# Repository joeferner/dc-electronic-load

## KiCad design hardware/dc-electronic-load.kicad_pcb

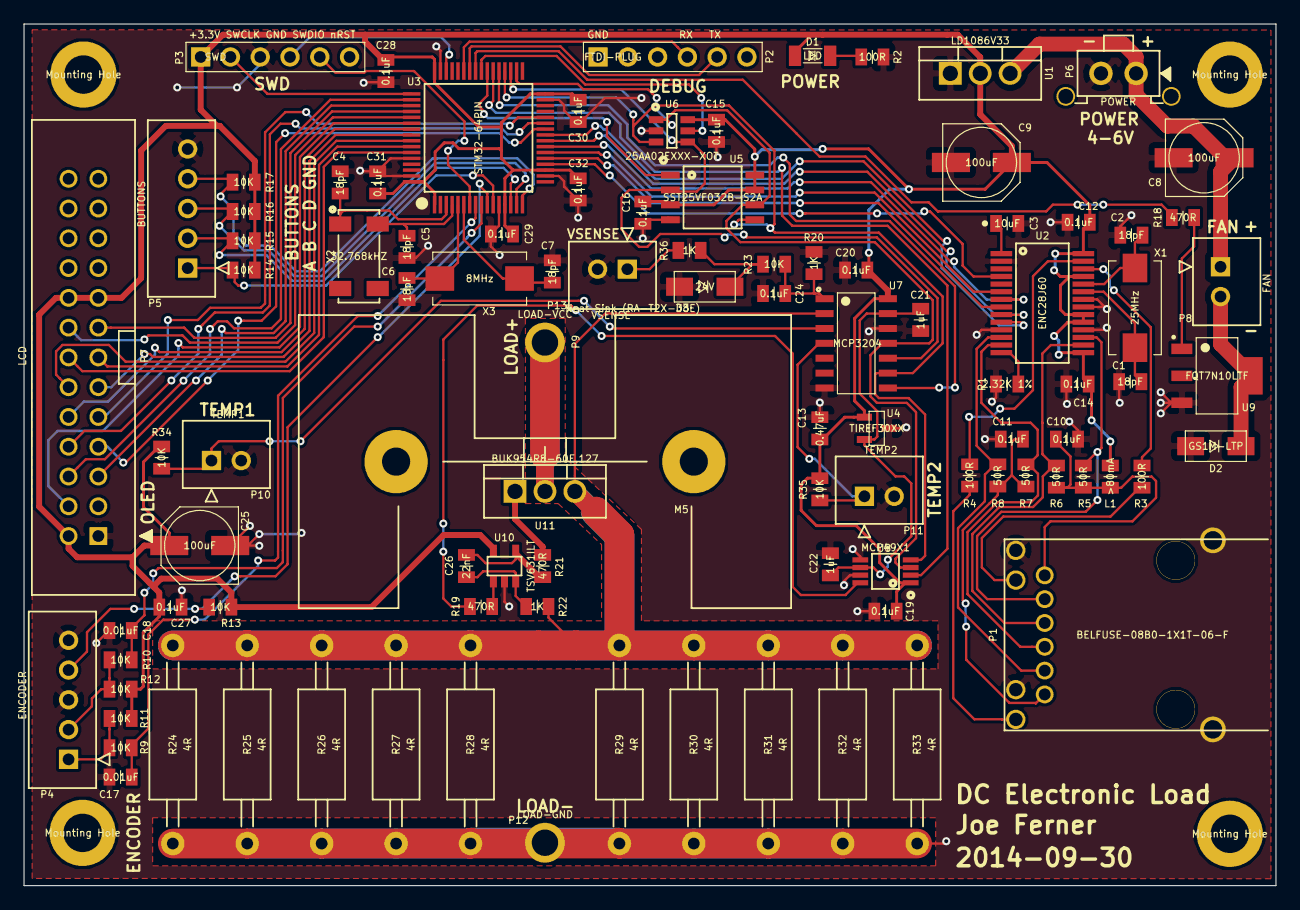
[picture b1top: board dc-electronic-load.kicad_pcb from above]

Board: 2 copper layers, 106.8 x 73.5 mm, 107 parts (0 on the bottom side), 78 nets.

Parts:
C1, C2, C4, C5, C6, C7: 18pF; CAPC2012X100N
C3: 10uF; CAPCP2012X100N
C8, C9, C25: 100uF; CAPAE660X790N
C10, C11, C12, C14, C15, C16, C19, C20, C24, C27, C28, C29, C30, C31, C32: 0.1uF; CAPC2012X100N
C13: 0.47uF; CAPC2012X100N
C17, C18: 0.01uF; CAPC2012X100N
C21, C22: 1uF; CAPC2012X100N
C26: 22nF; CAPC2012X100N
D1: LED; LEDC3216X100N
D2: GS1M-LTP; DIOM5226X220N
D3: 24V; DIOM5226X220N
L1: >80mA; RESC2012X100N
M1, M2, M3, M4: Mounting Hole; MTGNP565H328Z565P
M5: Heat Sink (RA-T2X-38E); OHMITE-R-SERIES
M6: Power Entry Connector; EMPTY
M7: Enclosure (8.36x9.11x3.15); EMPTY
M8: Fan (50mm x 10mm); EMPTY
M9: Fan Guard; EMPTY
P1: BELFUSE-08B0-1X1T-06-F; BEL-FUSE-08B0-1X1T-06-F
P2: FTDI-PLUG; HDRV6W66P254_1X6_1524X249X838P
P3: SWD; HDRV6W66P254_1X6_1524X249X838P
P4: ENCODER; JST-B5B-XH-A
P5: BUTTONS; JST-B5B-XH-A
P6: POWER; TECONN-2-1445050-2
P7: LCD; SHDRV26W100P254_2X13_4052X880X910P
P8: FAN; JST-B2B-XH-A
P9: LOAD-VCC; PAD205P
P10: TEMP1; JST-B2B-XH-A
P11: TEMP2; JST-B2B-XH-A
P12: LOAD-GND; PAD205P
P13: VSENSE; JST-B2B-XH-A
R1: 2.32K 1%; RESC2012X100N
R2, R3, R4: 100R; RESC2012X100N
R5, R6, R7, R8: 50R; RESC2012X100N
R9, R10, R11, R12, R13, R14, R15, R16, R17, R23, R34, R35: 10K; RESC2012X100N
R18, R19, R21: 470R; RESC2012X100N
R20, R22, R36: 1K; RESC2012X100N
R24, R25, R26, R27, R28, R29, R30, R31, R32, R33: 4R; RESAD1690W80L890D400P
U1: LD1086V33; TO255P460X1020X1925-3P
U2: ENC28J60; SOP65P780X200-28N
U3: STM32-64PIN; QFP50P1200X1200X160-64N
U4: TIREF30XX; SOT95P237X112_123-3N
U5: SST25VF032B-S2A; SOIC127P790X216-8N
U6: 25AA02EXXX-XOT; SOT95P270X145-6N
U7: MCP3204; SOIC127P600X175-14N
U8: MCP49X1; SOP65P490X110-8N
U9: FQT7N10LTF; SOT230P700X180-4N
U10: TSV631ILT; SOT95P280X100-5N
U11: BUK954R8-60E,127; TO255P460X1020X1925-3P
X1: 25MHz; XTAL8045X200N
X2: 32.768kHZ; SOJ550P370X240-4N
X3: 8MHz; XTAL8045X200N

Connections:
+3.3V: C9.1, C12.1, C13.1, C14.1, C15.1, C16.1, C19.1, C20.1, C25.1, C27.1, C28.1, C29.1, C30.1, C31.1, C32.1, D1.1, L1.1, P3.1, P7.2, P7.17, P7.18, R11.1, R12.1, R13.1, R14.1, R15.1, R16.1, R17.1, R34.2, R35.2, U1.2, U2.15, U2.19, U2.20, U2.25, U2.28, U3.1, U3.13, U3.19, U3.32, U3.48, U3.64, U4.1, U5.3, U5.7, U5.8, U6.6, U7.14, U8.1, U10.5
+5V: C8.1, P6.1, P8.1, U1.3
/ADCCS: U3.37, U7.8
/BUTTONA: P5.1, R14.2, U3.11
/BUTTONB: P5.2, R15.2, U3.14
/BUTTONC: P5.3, R16.2, U3.15
/BUTTOND: P5.4, R17.2, U3.16
/DACCS: U3.38, U8.2
/DEBUGRX: P2.4, U3.43
/DEBUGTX: P2.5, U3.42
/ENC28J60CS: U2.9, U3.24
/ENC28J60INT: U2.4, U3.20
/ENC28J60RESET: U2.10, U3.25
/ENCODERA: C17.1, R9.2, U3.8
/ENCODERB: C18.1, R10.2, U3.9
/ENCODERBUTTON: P4.4, R13.2, U3.10
/FAN: R18.2, U3.41
/FLASHCS: U3.39, U5.1
/ISENSE: R22.1, R24.1, R25.1, R26.1, R27.1, R28.1, R29.1, R30.1, R31.1, R32.1, R33.1, U7.2, U11.3
/LCDCS: P7.16, U3.53
/LCDDATA0: P7.7, U3.26
/LCDDATA1: P7.8, U3.27
/LCDDATA2: P7.9, U3.28
/LCDDATA3: P7.10, U3.55
/LCDDATA4: P7.11, U3.56
/LCDDATA5: P7.12, U3.57
/LCDDATA6: P7.13, U3.58
/LCDDATA7: P7.14, U3.59
/LCDDC: P7.4, U3.54
/LCDEN: P7.6, U3.50
/LCDRESET: P7.15, U3.52
/LCDRW: P7.5, U3.51
/MACCS: U3.40, U6.5
/SPI1MISO: U2.6, U3.22
/SPI1MOSI: U2.7, U3.23
/SPI1SCK: U2.8, U3.21
/SPI2MISO: U3.35, U5.2, U6.4, U7.10
/SPI2MOSI: U3.36, U5.5, U6.3, U7.9, U8.4
/SPI2SCK: U3.34, U5.6, U6.1, U7.11, U8.3
/SWCLK: P3.2, U3.49
/SWDIO: P3.4, U3.46
/TEMP1: P10.1, R34.1, U7.3
/TEMP2: P11.1, R35.1, U7.4
/VREF: C21.1, C22.1, U4.2, U7.13, U8.6
/VSENSE: C24.1, R20.2, R23.2, U7.1
/nRST: P3.5, U3.7
GNDPWR: C1.2, C2.2, C3.2, C4.2, C5.2, C6.2, C7.2, C8.2, C9.2, C10.2, C11.2, C12.2, C13.2, C14.2, C15.2, C16.2, C17.2, C18.2, C19.2, C20.2, C21.2, C22.2, C24.2, C25.2, C27.2, C28.2, C29.2, C30.2, C31.2, C32.2, D2.1, D3.1, P1.7, P1.9, P2.1, P3.3, P4.3, P4.5, P5.5, P6.2, P7.1, P10.2, P11.2, P12.1, P13.2, R1.2, R2.2, R20.1, R24.2, R25.2, R26.2, R27.2, R28.2, R29.2, R30.2, R31.2, R32.2, R33.2, U1.1, U2.2, U2.11, U2.18, U2.21, U2.22, U3.12, U3.18, U3.31, U3.47, U3.60, U3.63, U4.3, U5.4, U6.2, U7.7, U7.12, U8.5, U8.7, U9.3, U10.2
unnamed: C1.1, U2.23, X1.1
unnamed: C2.1, U2.24, X1.2
unnamed: C3.1, U2.1
unnamed: C4.1, U3.3, X2.1
unnamed: C5.1, U3.4, X2.4
unnamed: C6.1, U3.5, X3.1
unnamed: C7.1, U3.6, X3.2
unnamed: C10.1, L1.2, P1.1, R5.2, R6.1
unnamed: C11.1, P1.6, R7.2, R8.1
unnamed: C26.1, R21.2, U10.4
unnamed: C26.2, R22.2, U10.3
unnamed: D1.2, R2.1
unnamed: D2.2, P8.2, U9.4
unnamed: D3.2, R23.1, R36.2
unnamed: P1.2, R5.1, U2.17
unnamed: P1.3, R6.2, U2.16
unnamed: P1.4, R7.1, U2.13
unnamed: P1.5, R8.2, U2.12
unnamed: P1.8, R3.1
unnamed: P1.10, R4.1
unnamed: P4.1, R9.1, R11.2
unnamed: P4.2, R10.1, R12.2
unnamed: P9.1, U11.2
unnamed: P13.1, R36.1
unnamed: R1.1, U2.14
unnamed: R3.2, U2.26
unnamed: R4.2, U2.27
unnamed: R18.1, U9.1
unnamed: R19.1, U10.1
unnamed: R19.2, U8.8
unnamed: R21.1, U11.1

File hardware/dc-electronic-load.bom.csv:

,Reference, Value, Footprint, Datasheet, MfgPartNumber, Mfg,
x,C1,18pF,klib:CAPC2012X100N,,,,
x,C2,18pF,klib:CAPC2012X100N,,,,
x,C3,10uF,klib:CAPCP2012X100N,,,,
x,C4,18pF,klib:CAPC2012X100N,,,,
x,C5,18pF,klib:CAPC2012X100N,,,,
x,C6,18pF,klib:CAPC2012X100N,,,,
x,C7,18pF,klib:CAPC2012X100N,,,,
x,C8,100uF,klib:CAPAE660X790N,,,,
x,C9,100uF,klib:CAPAE660X790N,,,,
x,C10,0.1uF,klib:CAPC2012X100N,,,,
x,C11,0.1uF,klib:CAPC2012X100N,,,,
x,C12,0.1uF,klib:CAPC2012X100N,,,,
x,C13,0.47uF,klib:CAPC2012X100N,,,,
x,C14,0.1uF,klib:CAPC2012X100N,,,,
x,C15,0.1uF,klib:CAPC2012X100N,,,,
x,C16,0.1uF,klib:CAPC2012X100N,,,,
x,C17,0.01uF,klib:CAPC2012X100N,,,,
x,C18,0.01uF,klib:CAPC2012X100N,,,,
x,C19,0.1uF,klib:CAPC2012X100N,,,,
x,C20,0.1uF,klib:CAPC2012X100N,,,,
x,C21,1uF,klib:CAPC2012X100N,,,,
x,C22,1uF,klib:CAPC2012X100N,,,,
x,C24,0.1uF,klib:CAPC2012X100N,,,,
x,C25,100uF,klib:CAPAE660X790N,,,,
x,C26,22nF,klib:CAPC2012X100N,,,,
x,C27,0.1uF,klib:CAPC2012X100N,,,,
x,C28,0.1uF,klib:CAPC2012X100N,,,,
x,C29,0.1uF,klib:CAPC2012X100N,,,,
x,C30,0.1uF,klib:CAPC2012X100N,,,,
x,C31,0.1uF,klib:CAPC2012X100N,,,,
x,C32,0.1uF,klib:CAPC2012X100N,,,,
x,D1,LED,klib:LEDC3216X100N,,,,
x,D2,GS1M-LTP,klib:DIOM5226X220N,,GS1M-LTP,,
x,D3,24V,klib:DIOM5226X220N,,,,
x,L1,>80mA,klib:RESC2012X100N,,,,
x,M1,Mounting Hole,klib:MTGNP565H328Z565P,,,,
x,M2,Mounting Hole,klib:MTGNP565H328Z565P,,,,
x,M3,Mounting Hole,klib:MTGNP565H328Z565P,,,,
x,M4,Mounting Hole,klib:MTGNP565H328Z565P,,,,
x,M5,Heat Sink (RA-T2X-38E),klib:OHMITE-R-SERIES,,,,
x,M6,Power Entry Connector,klib:EMPTY,,06AK2D,,
x,M7,Enclosure (8.36x9.11x3.15),klib:EMPTY,,616-63210-510-000,PacTec,
x,M8,Fan (50mm x 10mm),klib:EMPTY,,MB50100V2-000U-A99,Sunon Fans,
x,M9,Fan Guard,klib:EMPTY,,FG-5,Sunon Fans,
x,P1,BELFUSE-08B0-1X1T-06-F,klib:BEL-FUSE-08B0-1X1T-06-F,,,,
x,P2,FTDI-PLUG,klib:HDRV6W66P254_1X6_1524X249X838P,,,,
x,P3,SWD,klib:HDRV6W66P254_1X6_1524X249X838P,,,,
x,P4,ENCODER,klib:JST-B5B-XH-A,,B5B-XH-A(LF)(SN),,
x,P5,BUTTONS,klib:JST-B5B-XH-A,,B5B-XH-A(LF)(SN),,
x,P6,POWER,klib:TECONN-2-1445050-2,,,,
x,P7,LCD,klib:SHDRV26W100P254_2X13_4052X880X910P,,,,
x,P8,FAN,klib:JST-B2B-XH-A,,,,
x,P9,LOAD-VCC,klib:PAD205P,,,,
x,P10,TEMP1,klib:JST-B2B-XH-A,,,,
x,P11,TEMP2,klib:JST-B2B-XH-A,,,,
x,P12,LOAD-GND,klib:PAD205P,,,,
x,P13,VSENSE,klib:JST-B2B-XH-A,,,,
x,R1,2.32K 1%,klib:RESC2012X100N,,,,
x,R2,100R,klib:RESC2012X100N,,,,
x,R3,100R,klib:RESC2012X100N,,,,
x,R4,100R,klib:RESC2012X100N,,,,
x,R5,50R,klib:RESC2012X100N,,,,
x,R6,50R,klib:RESC2012X100N,,,,
x,R7,50R,klib:RESC2012X100N,,,,
x,R8,50R,klib:RESC2012X100N,,,,
x,R9,10K,klib:RESC2012X100N,,,,
x,R10,10K,klib:RESC2012X100N,,,,
x,R11,10K,klib:RESC2012X100N,,,,
x,R12,10K,klib:RESC2012X100N,,,,
x,R13,10K,klib:RESC2012X100N,,,,
x,R14,10K,klib:RESC2012X100N,,,,
x,R15,10K,klib:RESC2012X100N,,,,
x,R16,10K,klib:RESC2012X100N,,,,
x,R17,10K,klib:RESC2012X100N,,,,
x,R18,470R,klib:RESC2012X100N,,,,
x,R19,470R,klib:RESC2012X100N,,,,
x,R20,1K,klib:RESC2012X100N,,,,
x,R21,470R,klib:RESC2012X100N,,,,
x,R22,1K,klib:RESC2012X100N,,,,
x,R23,10K,klib:RESC2012X100N,,,,
x,R24,4R,klib:RESAD1690W80L890D400P,,UB3C-4RF1,,
x,R25,4R,klib:RESAD1690W80L890D400P,,UB3C-4RF1,,
x,R26,4R,klib:RESAD1690W80L890D400P,,UB3C-4RF1,,
x,R27,4R,klib:RESAD1690W80L890D400P,,UB3C-4RF1,,
x,R28,4R,klib:RESAD1690W80L890D400P,,UB3C-4RF1,,
x,R29,4R,klib:RESAD1690W80L890D400P,,UB3C-4RF1,,
x,R30,4R,klib:RESAD1690W80L890D400P,,UB3C-4RF1,,
x,R31,4R,klib:RESAD1690W80L890D400P,,UB3C-4RF1,,
x,R32,4R,klib:RESAD1690W80L890D400P,,UB3C-4RF1,,
x,R33,4R,klib:RESAD1690W80L890D400P,,UB3C-4RF1,,
x,R34,10K,klib:RESC2012X100N,,,,
x,R35,10K,klib:RESC2012X100N,,,,
x,R36,1K,klib:RESC2012X100N,,,,
x,U1,LD1086V33,klib:TO255P460X1020X1925-3P,,,,
x,U2,ENC28J60,klib:SOP65P780X200-28N,,,,
x,U3,STM32-64PIN,klib:QFP50P1200X1200X160-64N,,,,
x,U4,TIREF30XX,klib:SOT95P237X112_123-3N,,,,
x,U5,SST25VF032B-S2A,klib:SOIC127P790X216-8N,,,,
x,U6,25AA02EXXX-XOT,klib:SOT95P270X145-6N,,,,
x,U7,MCP3204,klib:SOIC127P600X175-14N,,,,
x,U8,MCP49X1,klib:SOP65P490X110-8N,,,,
x,U9,FQT7N10LTF,klib:SOT230P700X180-4N,,FQT7N10LTF,,
x,U10,TSV631ILT,klib:SOT95P280X100-5N,,TSV631ILT,,
x,U11,BUK954R8-60E,127,klib:TO255P460X1020X1925-3P,,BUK954R8-60E,127
x,X1,25MHz,klib:XTAL8045X200N,,,,
x,X2,32.768kHZ,klib:SOJ550P370X240-4N,,,,
x,X3,8MHz,klib:XTAL8045X200N,,,,
x,,Thermister,,,,,

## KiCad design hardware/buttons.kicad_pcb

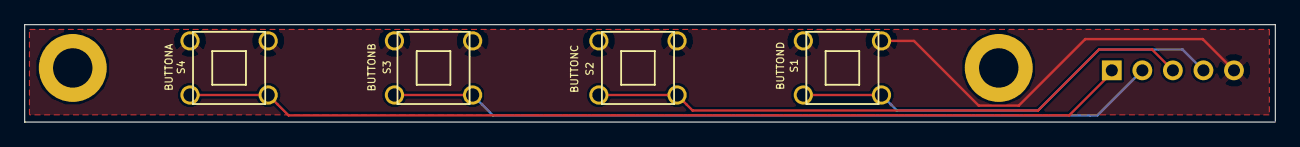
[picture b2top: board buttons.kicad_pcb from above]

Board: 2 copper layers, 104.0 x 8.1 mm, 7 parts (1 on the bottom side), 5 nets.

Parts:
M1, M2: Mounting Hole; MTGNP565H328Z565P
P1: P05; JST-B5B-XH-A
S1: BUTTOND; TL1105SP
S2: BUTTONC; TL1105SP
S3: BUTTONB; TL1105SP
S4: BUTTONA; TL1105SP

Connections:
GNDPWR: P1.5, S1.3, S1.4, S2.3, S2.4, S3.3, S3.4, S4.3, S4.4
unnamed: P1.1, S4.1, S4.2
unnamed: P1.2, S3.1, S3.2
unnamed: P1.3, S2.1, S2.2
unnamed: P1.4, S1.1, S1.2

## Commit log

2014-08-22 initial
2014-08-22 usart recv working
2014-08-22 change debug_tick to a process
2014-08-22 display starting to work
2014-08-22 refactor and faster
2014-08-22 clear on start
2014-08-22 initial gfx working
2014-08-24 working font
2014-08-24 faster redraw
2014-08-24 small font
2014-08-25 encoder test success
2014-08-26 switch polarity on encoder logic
2014-08-26 working encoder
2014-08-26 print size
2014-08-26 print numbers
2014-08-27 convert to non-antialias
2014-08-27 working adc but broken gdb
2014-08-27 working gdb?
2014-08-27 change to etimer instead of polling for adC
2014-08-27 switch to kdevelop
2014-08-28 read current
2014-08-28 format files
2014-08-29 working dac
2014-08-30 display overflow
2014-08-31 refactor calibration to new functions
2014-08-31 inital system diagram
2014-09-03 working fan control
2014-09-05 initial hardware
2014-09-07 more schematic work
2014-09-07 more schematic
2014-09-09 initial schematic complete
2014-09-09 more module assigning
2014-09-10 add mechanical parts
2014-09-12 add voltage reg module and resistor module
2014-09-12 more footprints
2014-09-12 add diode
2014-09-13 resistors
2014-09-30 pcb 2014-09-30
2014-10-01 add more enable/disable defines
2014-10-04 switch to network
2014-10-04 upgrade contiki
2014-10-04 httpd working
2014-10-05 working memory
2014-10-05 working read write debug commands
2014-10-06 flash upload working
2014-10-06 files
2014-10-07 working flash
2014-10-07 almost working httpd
2014-10-07 working httpd
2014-10-07 move spi setup
2014-10-07 support directories in flash files
2014-10-07 test ws server
2014-10-08 dynamic scripts and mime types
2014-10-10 graph working
2014-10-11 working mac
2014-10-12 working adc and dac
2014-10-13 working network and fan
2014-10-14 remove fan pwm
2014-10-19 working assembly
2014-10-20 add watts to display
2014-10-22 working http
2014-10-23 fix post request handling
2014-10-23 set amps
2014-10-24 working web sockets
2014-10-25 fix adc polling too often
2014-10-26 more ws
2014-10-26 working web socket disconnect
2014-11-09 try split
2014-11-09 initial buttons pcb
2014-11-10 buttons 2014-11-09
2014-11-11 menu works
2014-11-13 working recorder
2014-11-15 set rate of recording
2014-11-15 display version in info screen
2014-11-15 add info route
2014-11-15 remove telnet server
2014-11-16 add totals to build output
2014-11-16 add remaining to build
2014-11-16 remove generated version.h file
2014-11-16 ignore generated version.h file
2014-11-20 fix button assignment
2014-12-13 fix disable JTAG when not using GDB
2014-12-13 update part numbers
